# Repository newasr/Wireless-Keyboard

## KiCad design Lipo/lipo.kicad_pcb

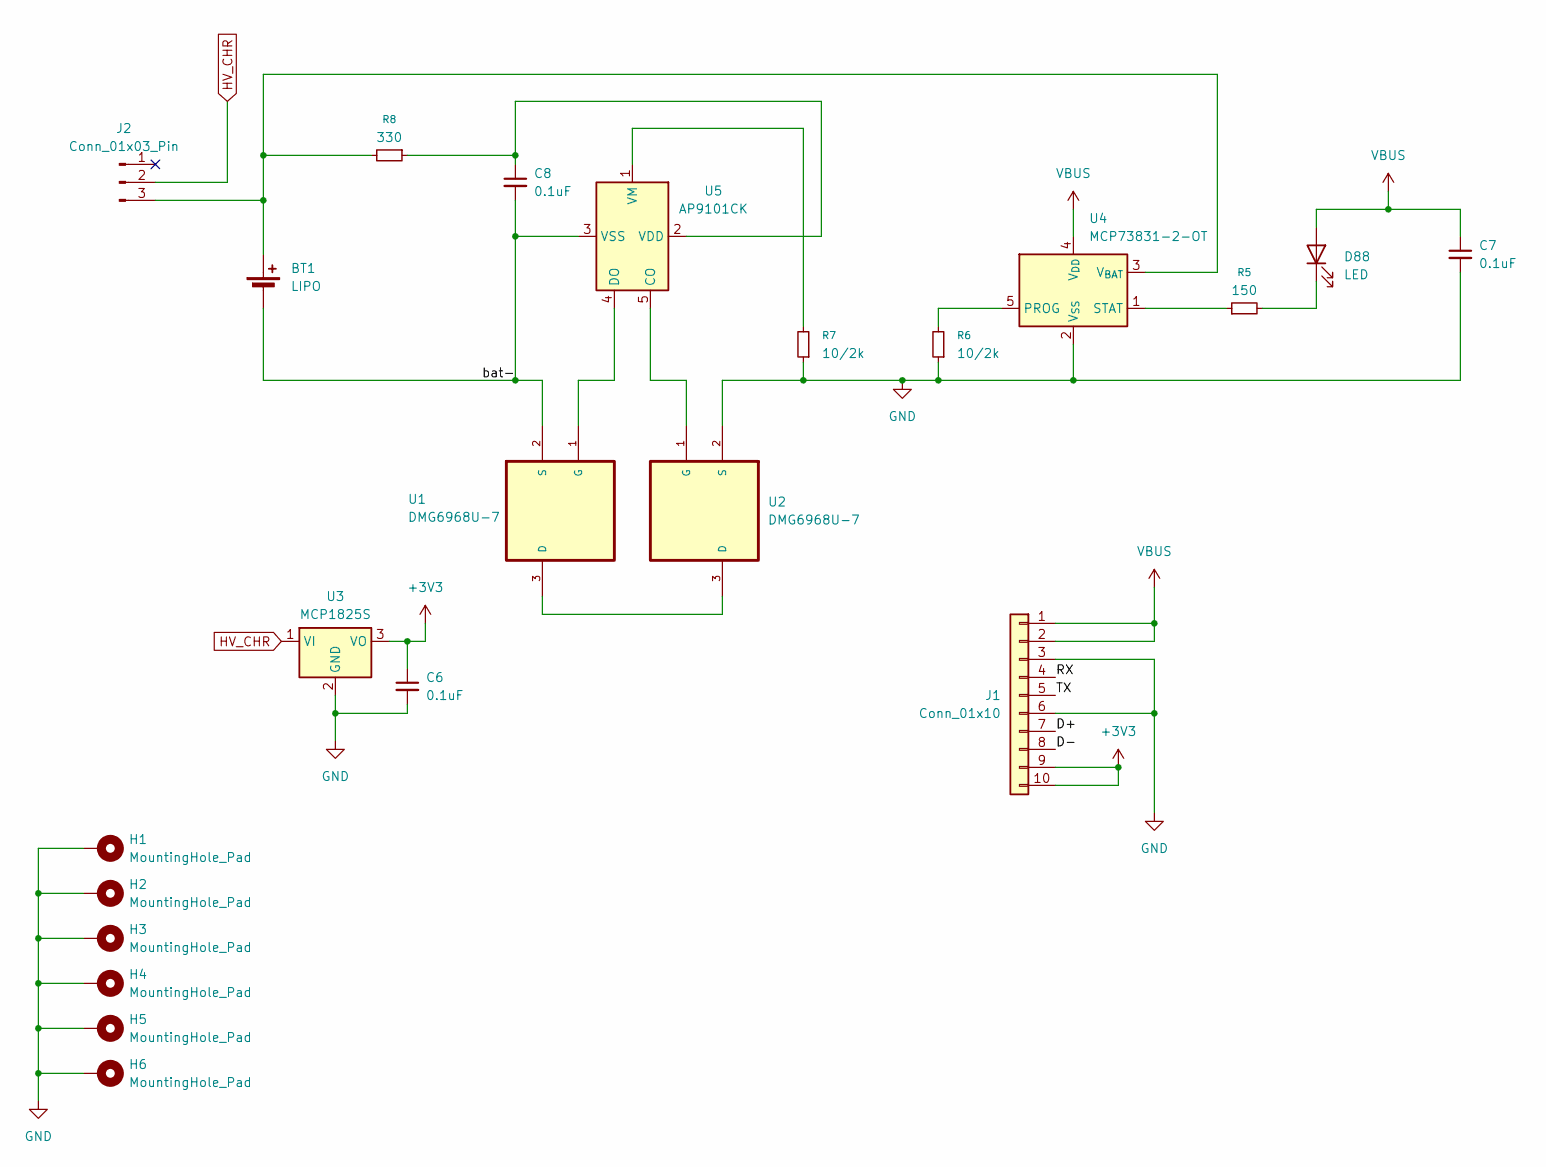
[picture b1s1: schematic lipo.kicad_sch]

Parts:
BT1: LIPO; PinHeader_1x02_P2.54mm_Vertical_SMD_Pin1Left
C6, C7, C8: 0.1uF; C_0201_0603Metric
D88: LED; LED_0603_1608Metric
H1, H2, H3, H4, H5, H6: MountingHole_Pad; MountingHole_3.2mm_M3_DIN965_Pad
J1: Conn_01x10; Molex_200528-0100_1x10-1MP_P1.00mm_Horizontal
J2: Conn_01x03_Pin; PinHeader_1x03_P2.54mm_Vertical_SMD_Pin1Left
R5: 150; R_0201_0603Metric
R6, R7: 10/2k; R_0201_0603Metric
R8: 330; R_0201_0603Metric
U1, U2: DMG6968U-7; dmg6968U7; MPN DMG6968U-7
U3: MCP1825S; SOT-223-3_TabPin2
U4: MCP73831-2-OT; SOT-23-5
U5: AP9101CK; SOT-23-5

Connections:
+3V3: C6.1, J1.9, J1.10, U3.3 (VO)
/D+: J1.7
/D-: J1.8
/RX: J1.4
/TX: J1.5
/bat-: BT1.2 (-), C8.2, U1.2 (S), U5.3 (VSS)
GND: C6.2, C7.2, H1.1, H2.1, H3.1, H4.1, H5.1, H6.1, J1.3, J1.6, R6.1, R7.1, U2.2 (S), U3.2 (GND), U4.2 (V_{SS})
HV_CHR: J2.2, U3.1 (VI)
unnamed: BT1.1 (+), J2.3, R8.2, U4.3 (V_{BAT})
unnamed: D88.1 (K), R5.2
unnamed: U1.3 (D), U2.3 (D)
unnamed: U1.1 (G), U5.4 (DO)
unnamed: U2.1 (G), U5.5 (CO)
unnamed: R6.2, U4.5 (PROG)
unnamed: R5.1, U4.1 (STAT)
unnamed: C8.1, R8.1, U5.2 (VDD)
unnamed: R7.2, U5.1 (VM)
VBUS: C7.1, D88.2 (A), J1.1, J1.2, U4.4 (V_{DD})

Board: 2 copper layers, 22 parts (0 on the bottom side), 14 nets, no tracks yet.

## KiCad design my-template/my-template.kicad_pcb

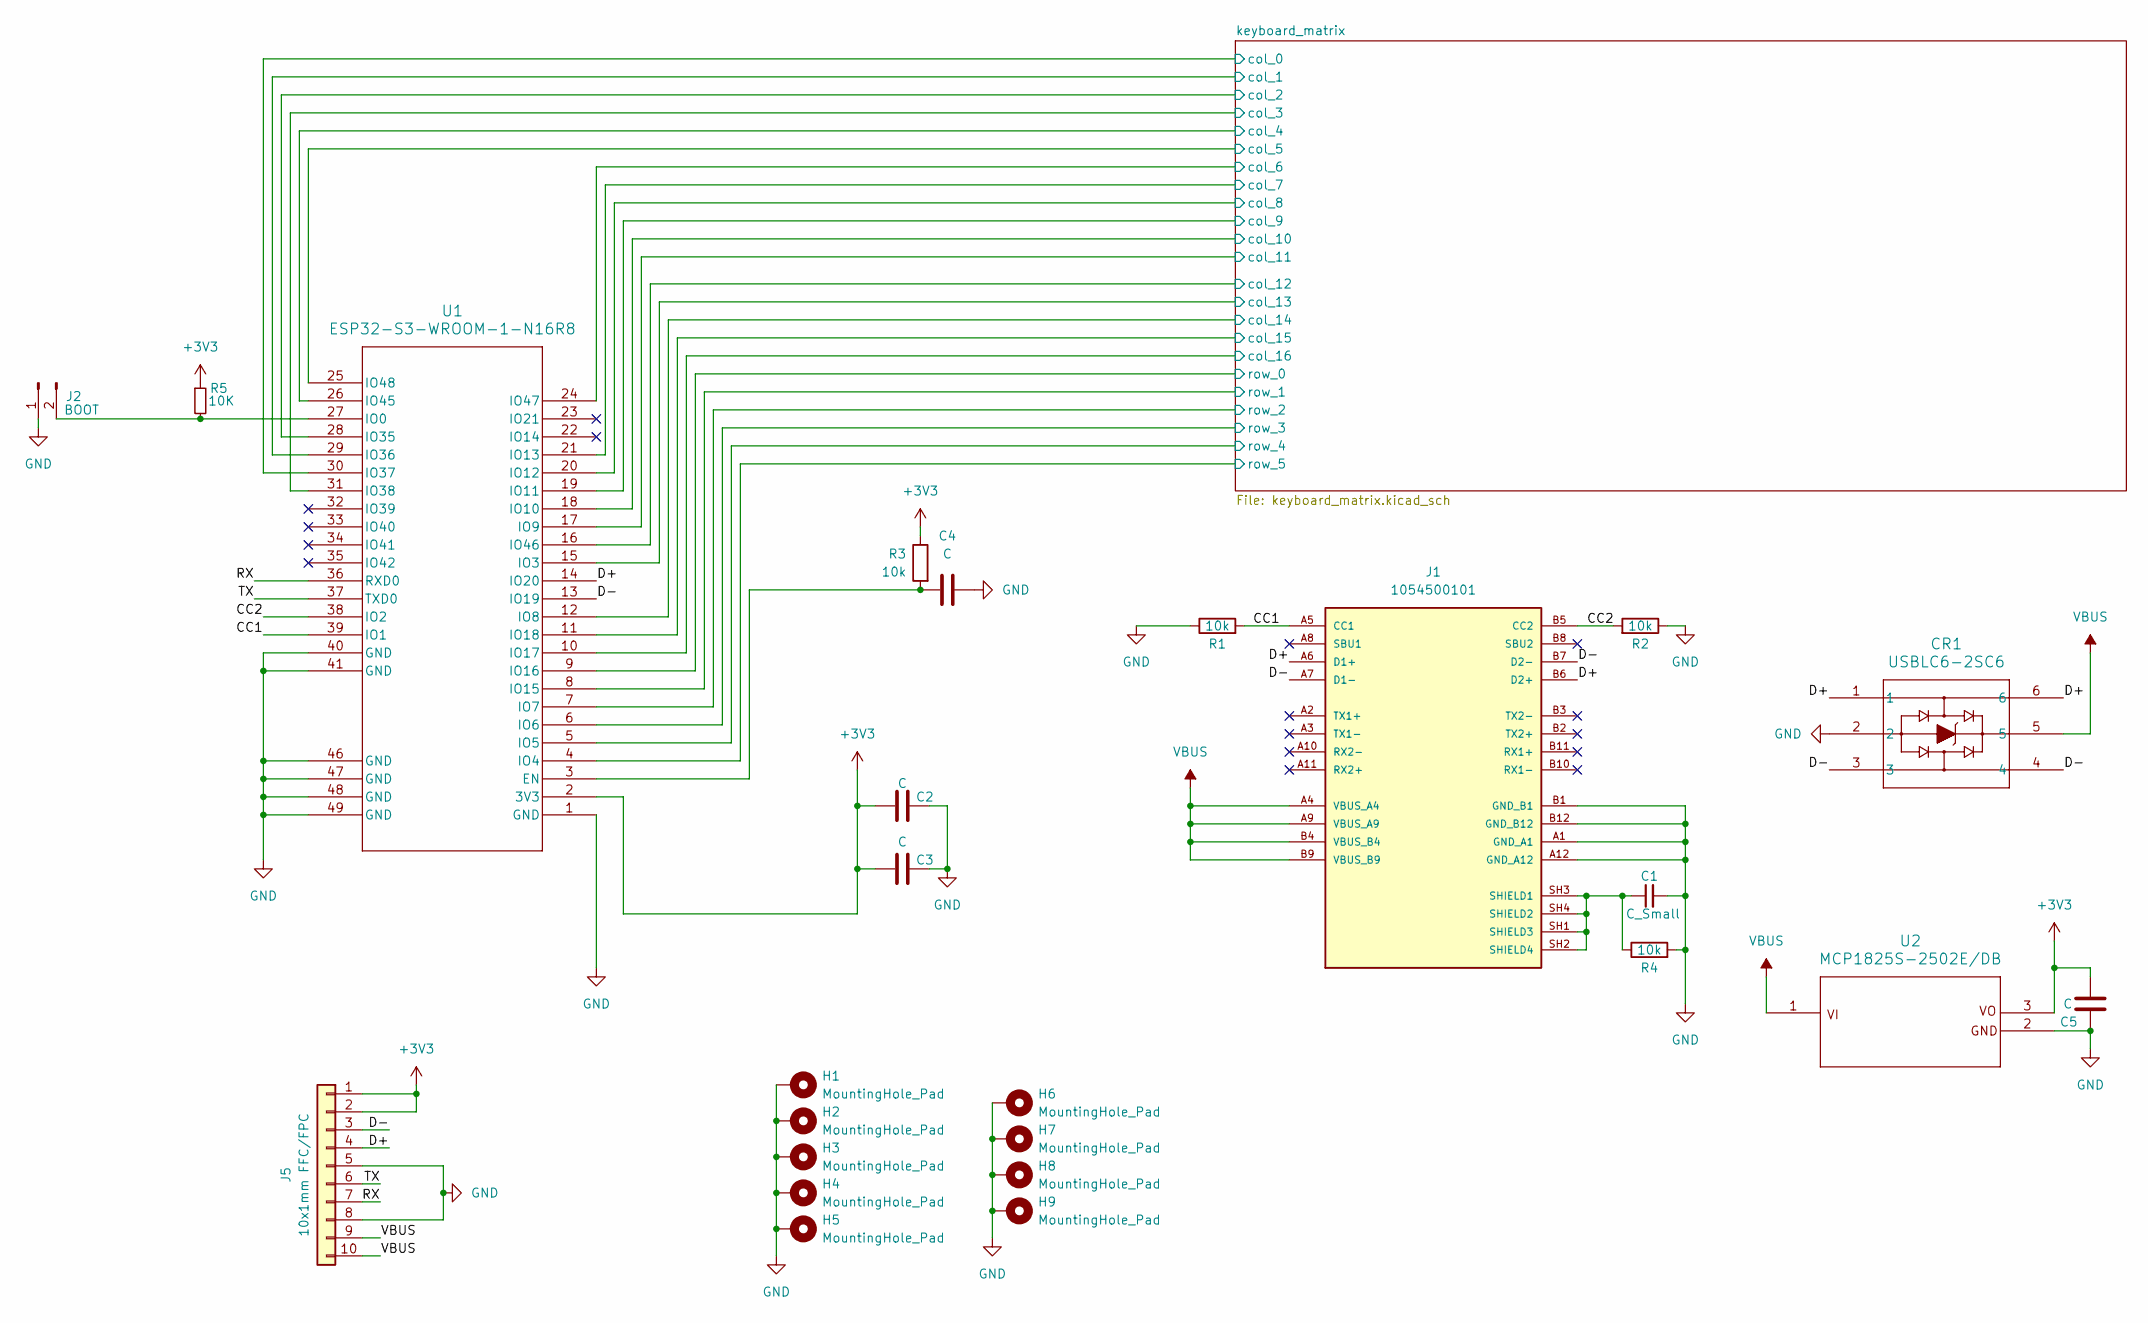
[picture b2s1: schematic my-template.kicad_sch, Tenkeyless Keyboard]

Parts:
C1: C_Small; C_0603_1608Metric
C2, C3, C4, C5: C; C_0603_1608Metric
CR1: USBLC6-2SC6
H1, H2, H3, H4, H5, H6, H7, H8, H9: MountingHole_Pad; MountingHole_3.2mm_M3_DIN965_Pad
J1: 1054500101; MOLEX_1054500101; PARTREV A7
J2: BOOT; PinHeader_1x02_P2.54mm_Horizontal
J5: 10x1mm FFC/FPC; Molex_200528-0100_1x10-1MP_P1.00mm_Horizontal
R1, R2, R3, R4: 10k; R_0603_1608Metric
R5: 10K; R_0603_1608Metric
U1: ESP32-S3-WROOM-1-N16R8; ESP32-S3-WROOM-1_EXP
U2: MCP1825S-2502E/DB; SOT-223_3MC_MCH

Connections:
+3V3: C2.1, C3.1, C5.1, J5.1, J5.2, R3.1, R5.1, U1.2 (3V3), U2.3
/CC1: J1.A5 (CC1), R1.2, U1.39 (IO1)
/CC2: J1.B5 (CC2), R2.2, U1.38 (IO2)
/D+: CR1.1, CR1.6, J1.A6 (D1+), J1.B6 (D2+), J5.4, U1.14 (IO20)
/D-: CR1.3, CR1.4, J1.A7 (D1-), J1.B7 (D2-), J5.3, U1.13 (IO19)
/RX: J5.7, U1.36 (RXD0)
/TX: J5.6, U1.37 (TXD0)
/keyboard_matrix/col_0: U1.30 (IO37); also elsewhere on the board
/keyboard_matrix/col_1: U1.29 (IO36); also elsewhere on the board
/keyboard_matrix/col_2: U1.28 (IO35); also elsewhere on the board
/keyboard_matrix/col_3: U1.31 (IO38); also elsewhere on the board
/keyboard_matrix/col_4: U1.26 (IO45); also elsewhere on the board
/keyboard_matrix/col_5: U1.25 (IO48); also elsewhere on the board
/keyboard_matrix/col_6: U1.24 (IO47); also elsewhere on the board
/keyboard_matrix/col_7: U1.21 (IO13); also elsewhere on the board
/keyboard_matrix/col_8: U1.20 (IO12); also elsewhere on the board
/keyboard_matrix/col_9: U1.19 (IO11); also elsewhere on the board
/keyboard_matrix/col_10: U1.18 (IO10); also elsewhere on the board
/keyboard_matrix/col_11: U1.17 (IO9); also elsewhere on the board
/keyboard_matrix/col_12: U1.16 (IO46); also elsewhere on the board
/keyboard_matrix/col_13: U1.15 (IO3); also elsewhere on the board
/keyboard_matrix/col_14: U1.12 (IO8); also elsewhere on the board
/keyboard_matrix/col_15: U1.11 (IO18); also elsewhere on the board
/keyboard_matrix/col_16: U1.10 (IO17); also elsewhere on the board
/keyboard_matrix/row_0: U1.9 (IO16); also elsewhere on the board
/keyboard_matrix/row_1: U1.8 (IO15); also elsewhere on the board
/keyboard_matrix/row_2: U1.7 (IO7); also elsewhere on the board
/keyboard_matrix/row_3: U1.6 (IO6); also elsewhere on the board
/keyboard_matrix/row_4: U1.5 (IO5); also elsewhere on the board
/keyboard_matrix/row_5: U1.4 (IO4); also elsewhere on the board
GND: C1.2, C2.2, C3.2, C4.2, C5.2, CR1.2, H1.1, H2.1, H3.1, H4.1, H5.1, H6.1, H7.1, H8.1, H9.1, J1.A1 (GND_A1), J1.A12 (GND_A12), J1.B1 (GND_B1), J1.B12 (GND_B12), J2.1, J5.5, J5.8, R1.1, R2.1, R4.2, U1.1 (GND), U1.40 (GND), U1.41 (GND), U1.46 (GND), U1.47 (GND), U1.48 (GND), U1.49 (GND), U2.2
unnamed: C1.1, J1.SH1 (SHIELD3), J1.SH2 (SHIELD4), J1.SH3 (SHIELD1), J1.SH4 (SHIELD2), R4.1
unnamed: J2.2, R5.2, U1.27 (IO0)
unnamed: C4.1, R3.2, U1.3 (EN)
VBUS: CR1.5, J1.A4 (VBUS_A4), J1.A9 (VBUS_A9), J1.B4 (VBUS_B4), J1.B9 (VBUS_B9), J5.9, J5.10, U2.1

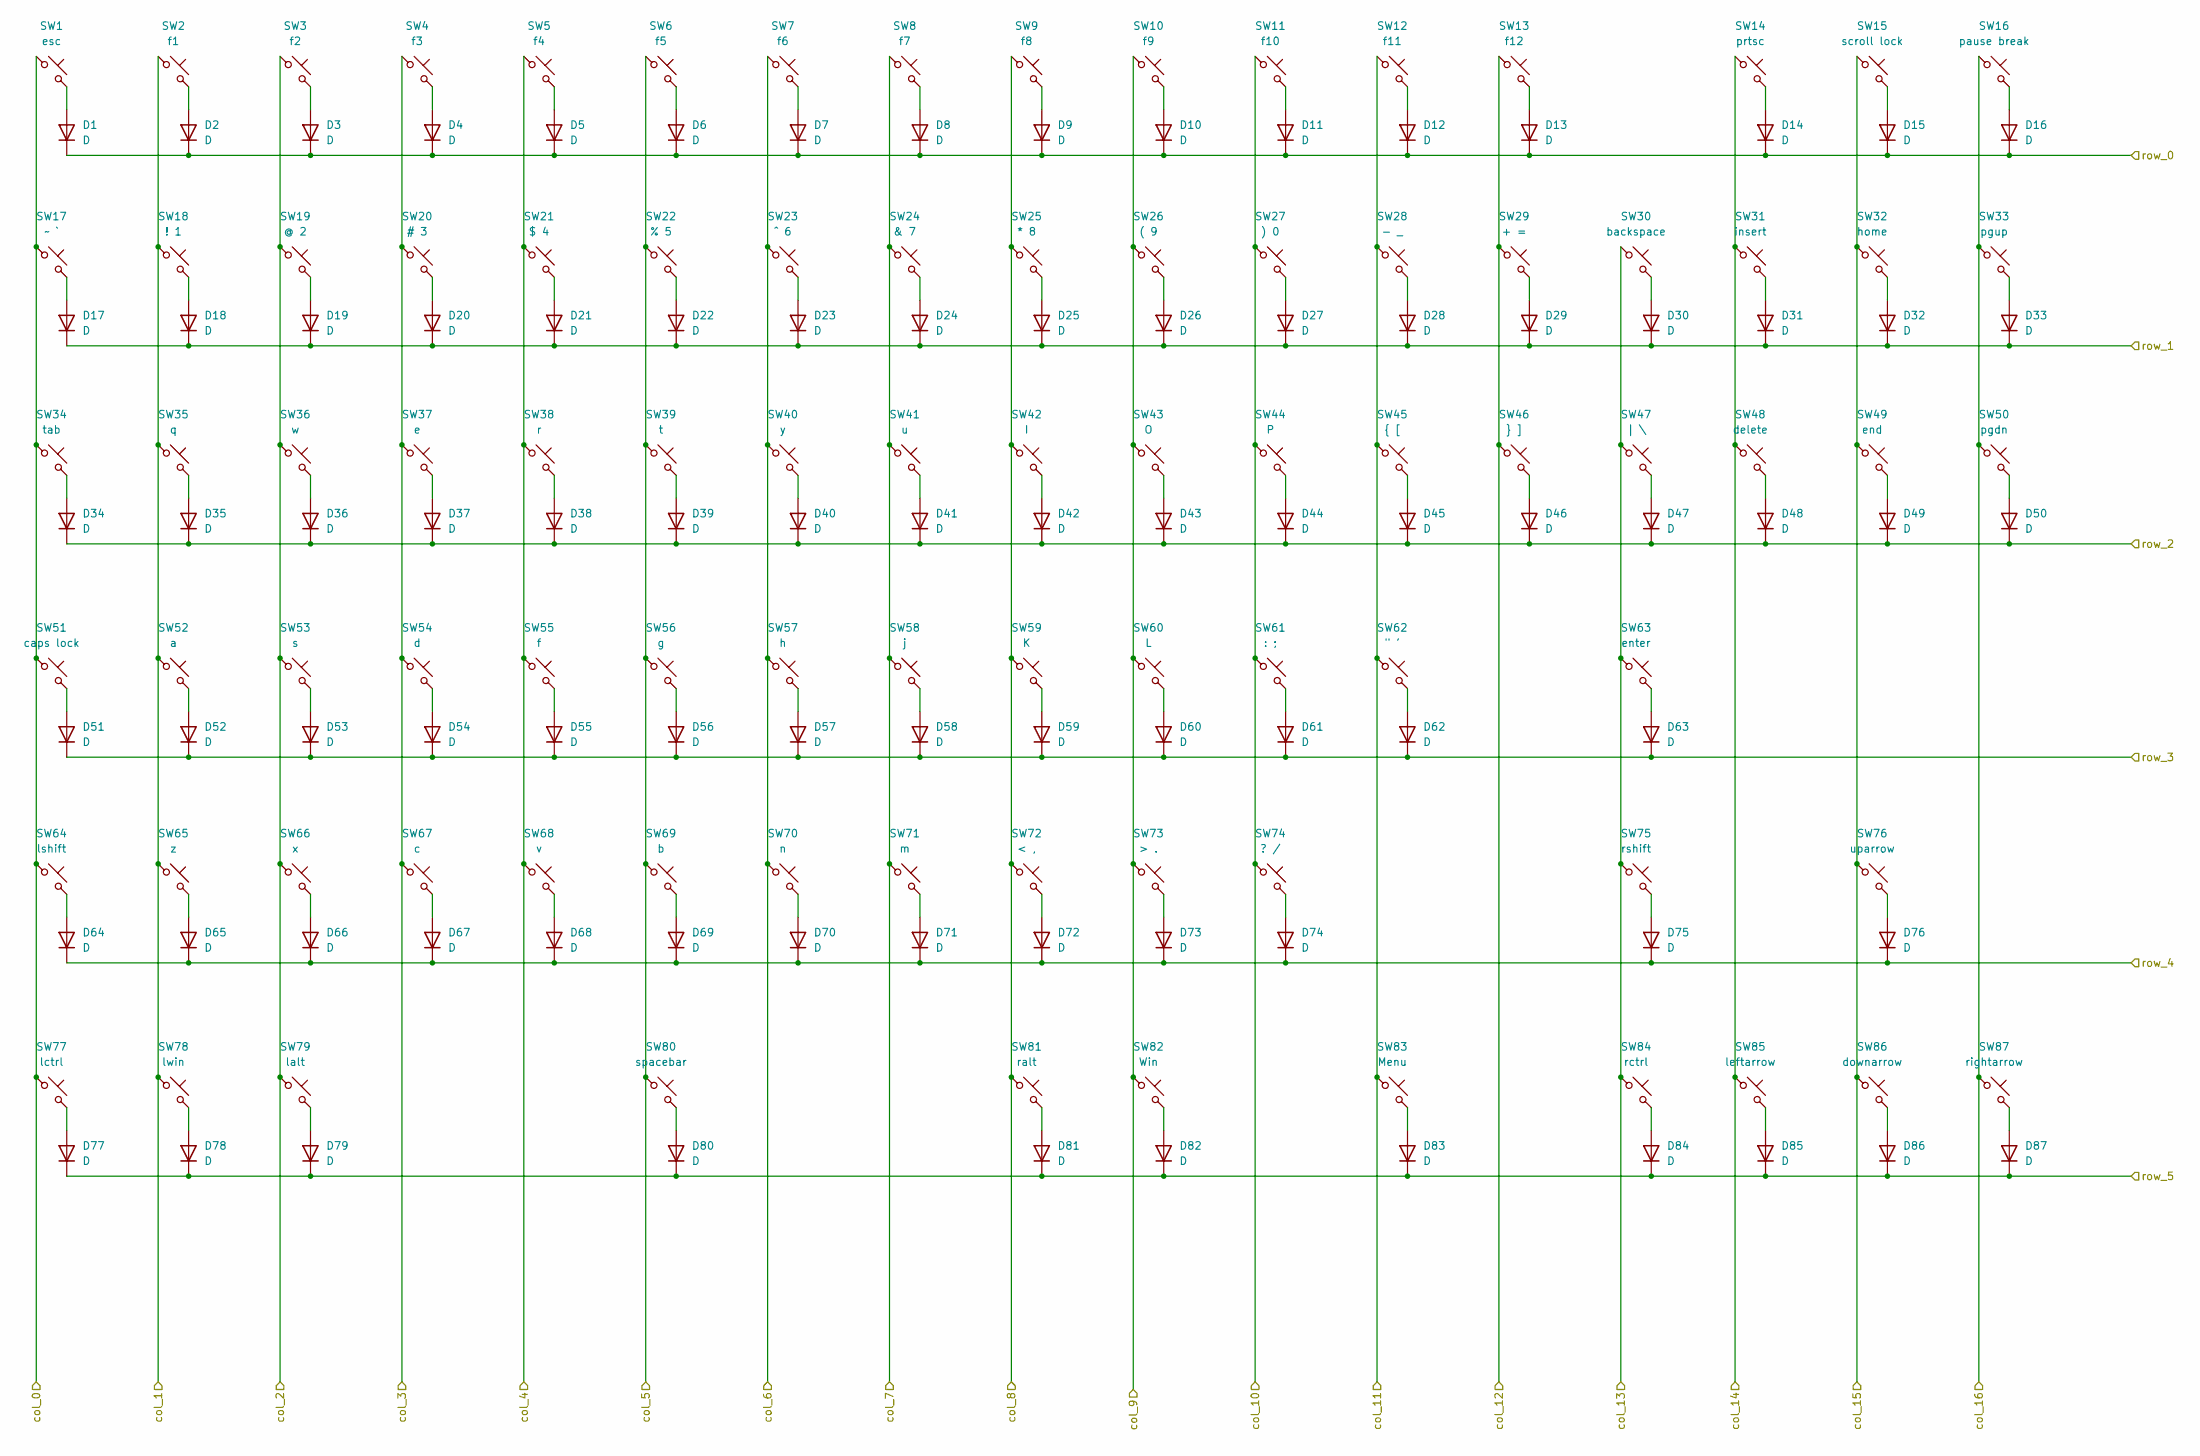
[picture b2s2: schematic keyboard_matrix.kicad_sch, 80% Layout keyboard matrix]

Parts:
D1, D2, D3, D4, D5, D6, D7, D8, D9, D10, D11, D12, D13, D14, D15, D16, D17, D18, D19, D20, D21, D22, D23, D24, D25, D26, D27, D28, D29, D30, D31, D32, D33, D34, D35, D36, D37, D38, D39, D40, D41, D42, D43, D44, D45, D46, D47, D48, D49, D50, D51, D52, D53, D54, D55, D56, D57, D58, D59, D60, D61, D62, D63, D64, D65, D66, D67, D68, D69, D70, D71, D72, D73, D74, D75, D76, D77, D78, D79, D80, D81, D82, D83, D84, D85, D86, D87: D; D_SOD-123
SW1: esc; MX_PCB_1.00u
SW2: f1; MX_PCB_1.00u
SW3: f2; MX_PCB_1.00u
SW4: f3; MX_PCB_1.00u
SW5: f4; MX_PCB_1.00u
SW6: f5; MX_PCB_1.00u
SW7: f6; MX_PCB_1.00u
SW8: f7; MX_PCB_1.00u
SW9: f8; MX_PCB_1.00u
SW10: f9; MX_PCB_1.00u
SW11: f10; MX_PCB_1.00u
SW12: f11; MX_PCB_1.00u
SW13: f12; MX_PCB_1.00u
SW14: prtsc; MX_PCB_1.00u
SW15: scroll lock; MX_PCB_1.00u
SW16: pause break; MX_PCB_1.00u
SW17: ~ `; MX_PCB_1.00u
SW18: ! 1; MX_PCB_1.00u
SW19: @ 2; MX_PCB_1.00u
SW20: # 3; MX_PCB_1.00u
SW21: $ 4; MX_PCB_1.00u
SW22: % 5; MX_PCB_1.00u
SW23: ^ 6; MX_PCB_1.00u
SW24: & 7; MX_PCB_1.00u
SW25: * 8; MX_PCB_1.00u
SW26: ( 9; MX_PCB_1.00u
SW27: ) 0; MX_PCB_1.00u
SW28: - _; MX_PCB_1.00u
SW29: + =; MX_PCB_1.00u
SW30: backspace; MX_PCB_2.00u
SW31: insert; MX_PCB_1.00u
SW32: home; MX_PCB_1.00u
SW33: pgup; MX_PCB_1.00u
SW34: tab; MX_PCB_1.50u
SW35: q; MX_PCB_1.00u
SW36: w; MX_PCB_1.00u
SW37: e; MX_PCB_1.00u
SW38: r; MX_PCB_1.00u
SW39: t; MX_PCB_1.00u
SW40: y; MX_PCB_1.00u
SW41: u; MX_PCB_1.00u
SW42: I; MX_PCB_1.00u
SW43: O; MX_PCB_1.00u
SW44: P; MX_PCB_1.00u
SW45: { [; MX_PCB_1.00u
SW46: } ]; MX_PCB_1.00u
SW47: | \; MX_PCB_1.50u
SW48: delete; MX_PCB_1.00u
SW49: end; MX_PCB_1.00u
SW50: pgdn; MX_PCB_1.00u
SW51: caps lock; MX_PCB_1.00u
SW52: a; MX_PCB_1.00u
SW53: s; MX_PCB_1.00u
SW54: d; MX_PCB_1.00u
SW55: f; MX_PCB_1.00u
SW56: g; MX_PCB_1.00u
SW57: h; MX_PCB_1.00u
SW58: j; MX_PCB_1.00u
SW59: K; MX_PCB_1.00u
SW60: L; MX_PCB_1.00u
SW61: : ;; MX_PCB_1.00u
SW62: " '; MX_PCB_1.00u
SW63: enter; MX_PCB_2.25u
SW64: lshift; MX_PCB_2.25u
SW65: z; MX_PCB_1.00u
SW66: x; MX_PCB_1.00u
SW67: c; MX_PCB_1.00u
SW68: v; MX_PCB_1.00u
SW69: b; MX_PCB_1.00u
SW70: n; MX_PCB_1.00u
SW71: m; MX_PCB_1.00u
SW72: < ,; MX_PCB_1.00u
SW73: > .; MX_PCB_1.00u
SW74: ? /; MX_PCB_1.00u
SW75: rshift; MX_PCB_2.75u
SW76: uparrow; MX_PCB_1.00u
SW77: lctrl; MX_PCB_1.25u
SW78: lwin; MX_PCB_1.25u
SW79: lalt; MX_PCB_1.25u
SW80: spacebar; MX_PCB_6.25u
SW81: ralt; MX_PCB_1.25u
SW82: Win; MX_PCB_1.25u
SW83: Menu; MX_PCB_1.25u
SW84: rctrl; MX_PCB_1.25u
SW85: leftarrow; MX_PCB_1.00u
SW86: downarrow; MX_PCB_1.00u
SW87: rightarrow; MX_PCB_1.00u

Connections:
/keyboard_matrix/col_0: SW1.1, SW17.1, SW34.1, SW51.1, SW64.1, SW77.1; also elsewhere on the board
/keyboard_matrix/col_1: SW2.1, SW18.1, SW35.1, SW52.1, SW65.1, SW78.1; also elsewhere on the board
/keyboard_matrix/col_2: SW3.1, SW19.1, SW36.1, SW53.1, SW66.1, SW79.1; also elsewhere on the board
/keyboard_matrix/col_3: SW4.1, SW20.1, SW37.1, SW54.1, SW67.1; also elsewhere on the board
/keyboard_matrix/col_4: SW5.1, SW21.1, SW38.1, SW55.1, SW68.1; also elsewhere on the board
/keyboard_matrix/col_5: SW6.1, SW22.1, SW39.1, SW56.1, SW69.1, SW80.1; also elsewhere on the board
/keyboard_matrix/col_6: SW7.1, SW23.1, SW40.1, SW57.1, SW70.1; also elsewhere on the board
/keyboard_matrix/col_7: SW8.1, SW24.1, SW41.1, SW58.1, SW71.1; also elsewhere on the board
/keyboard_matrix/col_8: SW9.1, SW25.1, SW42.1, SW59.1, SW72.1, SW81.1; also elsewhere on the board
/keyboard_matrix/col_9: SW10.1, SW26.1, SW43.1, SW60.1, SW73.1, SW82.1; also elsewhere on the board
/keyboard_matrix/col_10: SW11.1, SW27.1, SW44.1, SW61.1, SW74.1; also elsewhere on the board
/keyboard_matrix/col_11: SW12.1, SW28.1, SW45.1, SW62.1, SW83.1; also elsewhere on the board
/keyboard_matrix/col_12: SW13.1, SW29.1, SW46.1; also elsewhere on the board
/keyboard_matrix/col_13: SW30.1, SW47.1, SW63.1, SW75.1, SW84.1; also elsewhere on the board
/keyboard_matrix/col_14: SW14.1, SW31.1, SW48.1, SW85.1; also elsewhere on the board
/keyboard_matrix/col_15: SW15.1, SW32.1, SW49.1, SW76.1, SW86.1; also elsewhere on the board
/keyboard_matrix/col_16: SW16.1, SW33.1, SW50.1, SW87.1; also elsewhere on the board
/keyboard_matrix/row_0: D1.1 (K), D2.1 (K), D3.1 (K), D4.1 (K), D5.1 (K), D6.1 (K), D7.1 (K), D8.1 (K), D9.1 (K), D10.1 (K), D11.1 (K), D12.1 (K), D13.1 (K), D14.1 (K), D15.1 (K), D16.1 (K); also elsewhere on the board
/keyboard_matrix/row_1: D17.1 (K), D18.1 (K), D19.1 (K), D20.1 (K), D21.1 (K), D22.1 (K), D23.1 (K), D24.1 (K), D25.1 (K), D26.1 (K), D27.1 (K), D28.1 (K), D29.1 (K), D30.1 (K), D31.1 (K), D32.1 (K), D33.1 (K); also elsewhere on the board
/keyboard_matrix/row_2: D34.1 (K), D35.1 (K), D36.1 (K), D37.1 (K), D38.1 (K), D39.1 (K), D40.1 (K), D41.1 (K), D42.1 (K), D43.1 (K), D44.1 (K), D45.1 (K), D46.1 (K), D47.1 (K), D48.1 (K), D49.1 (K), D50.1 (K); also elsewhere on the board
/keyboard_matrix/row_3: D51.1 (K), D52.1 (K), D53.1 (K), D54.1 (K), D55.1 (K), D56.1 (K), D57.1 (K), D58.1 (K), D59.1 (K), D60.1 (K), D61.1 (K), D62.1 (K), D63.1 (K); also elsewhere on the board
/keyboard_matrix/row_4: D64.1 (K), D65.1 (K), D66.1 (K), D67.1 (K), D68.1 (K), D69.1 (K), D70.1 (K), D71.1 (K), D72.1 (K), D73.1 (K), D74.1 (K), D75.1 (K), D76.1 (K); also elsewhere on the board
/keyboard_matrix/row_5: D77.1 (K), D78.1 (K), D79.1 (K), D80.1 (K), D81.1 (K), D82.1 (K), D83.1 (K), D84.1 (K), D85.1 (K), D86.1 (K), D87.1 (K); also elsewhere on the board
unnamed: D1.2 (A), SW1.2
unnamed: D2.2 (A), SW2.2
unnamed: D3.2 (A), SW3.2
unnamed: D4.2 (A), SW4.2
unnamed: D5.2 (A), SW5.2
unnamed: D6.2 (A), SW6.2
unnamed: D7.2 (A), SW7.2
unnamed: D8.2 (A), SW8.2
unnamed: D9.2 (A), SW9.2
unnamed: D10.2 (A), SW10.2
unnamed: D11.2 (A), SW11.2
unnamed: D12.2 (A), SW12.2
unnamed: D13.2 (A), SW13.2
unnamed: D14.2 (A), SW14.2
unnamed: D15.2 (A), SW15.2
unnamed: D16.2 (A), SW16.2
unnamed: D17.2 (A), SW17.2
unnamed: D18.2 (A), SW18.2
unnamed: D19.2 (A), SW19.2
unnamed: D20.2 (A), SW20.2
unnamed: D21.2 (A), SW21.2
unnamed: D22.2 (A), SW22.2
unnamed: D23.2 (A), SW23.2
unnamed: D24.2 (A), SW24.2
unnamed: D25.2 (A), SW25.2
unnamed: D26.2 (A), SW26.2
unnamed: D27.2 (A), SW27.2
unnamed: D28.2 (A), SW28.2
unnamed: D29.2 (A), SW29.2
unnamed: D30.2 (A), SW30.2
unnamed: D31.2 (A), SW31.2
unnamed: D32.2 (A), SW32.2
unnamed: D33.2 (A), SW33.2
unnamed: D34.2 (A), SW34.2
unnamed: D35.2 (A), SW35.2
unnamed: D36.2 (A), SW36.2
unnamed: D37.2 (A), SW37.2
unnamed: D38.2 (A), SW38.2
unnamed: D39.2 (A), SW39.2
unnamed: D40.2 (A), SW40.2
unnamed: D41.2 (A), SW41.2
unnamed: D42.2 (A), SW42.2
unnamed: D43.2 (A), SW43.2
unnamed: D44.2 (A), SW44.2
unnamed: D45.2 (A), SW45.2
unnamed: D46.2 (A), SW46.2
unnamed: D47.2 (A), SW47.2
unnamed: D48.2 (A), SW48.2
unnamed: D49.2 (A), SW49.2
unnamed: D50.2 (A), SW50.2
unnamed: D51.2 (A), SW51.2
unnamed: D52.2 (A), SW52.2
unnamed: D53.2 (A), SW53.2
unnamed: D54.2 (A), SW54.2
unnamed: D55.2 (A), SW55.2
unnamed: D56.2 (A), SW56.2
unnamed: D57.2 (A), SW57.2
unnamed: D58.2 (A), SW58.2
unnamed: D59.2 (A), SW59.2
unnamed: D60.2 (A), SW60.2
unnamed: D61.2 (A), SW61.2
unnamed: D62.2 (A), SW62.2
unnamed: D63.2 (A), SW63.2
unnamed: D64.2 (A), SW64.2
unnamed: D65.2 (A), SW65.2
unnamed: D66.2 (A), SW66.2
unnamed: D67.2 (A), SW67.2
unnamed: D68.2 (A), SW68.2
unnamed: D69.2 (A), SW69.2
unnamed: D70.2 (A), SW70.2
unnamed: D71.2 (A), SW71.2
unnamed: D72.2 (A), SW72.2
unnamed: D73.2 (A), SW73.2
unnamed: D74.2 (A), SW74.2
unnamed: D75.2 (A), SW75.2
unnamed: D76.2 (A), SW76.2
unnamed: D77.2 (A), SW77.2
unnamed: D78.2 (A), SW78.2
unnamed: D79.2 (A), SW79.2
unnamed: D80.2 (A), SW80.2
unnamed: D81.2 (A), SW81.2
unnamed: D82.2 (A), SW82.2
unnamed: D83.2 (A), SW83.2
unnamed: D84.2 (A), SW84.2
unnamed: D85.2 (A), SW85.2
unnamed: D86.2 (A), SW86.2
unnamed: D87.2 (A), SW87.2

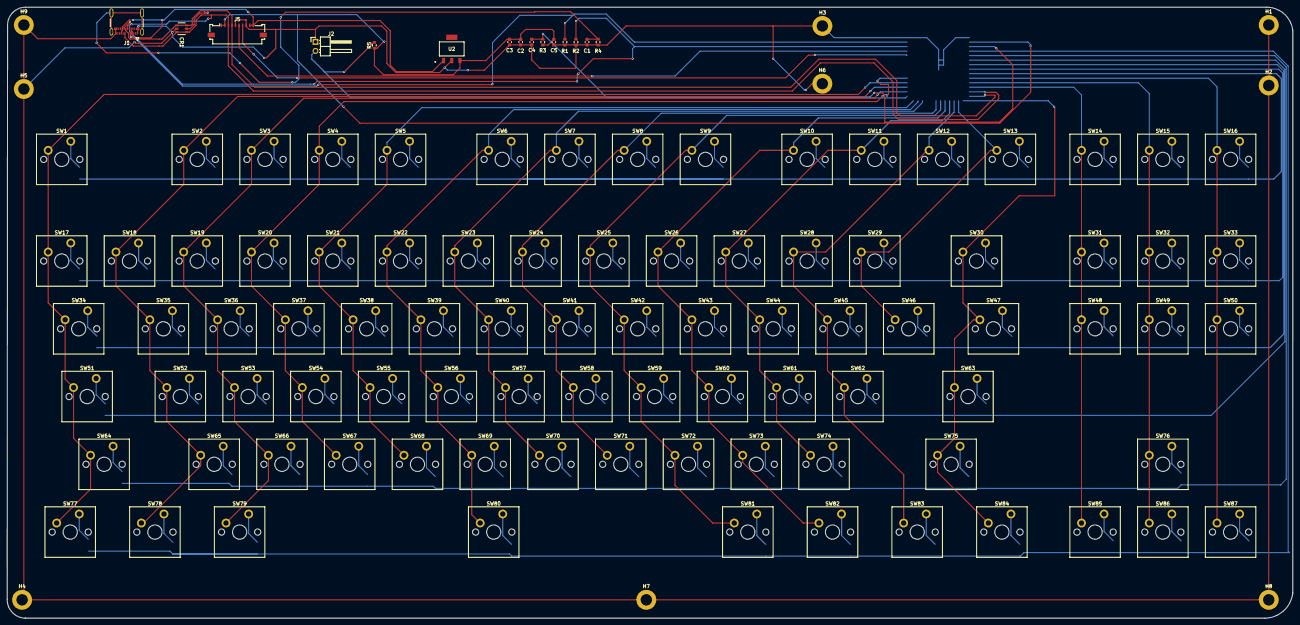
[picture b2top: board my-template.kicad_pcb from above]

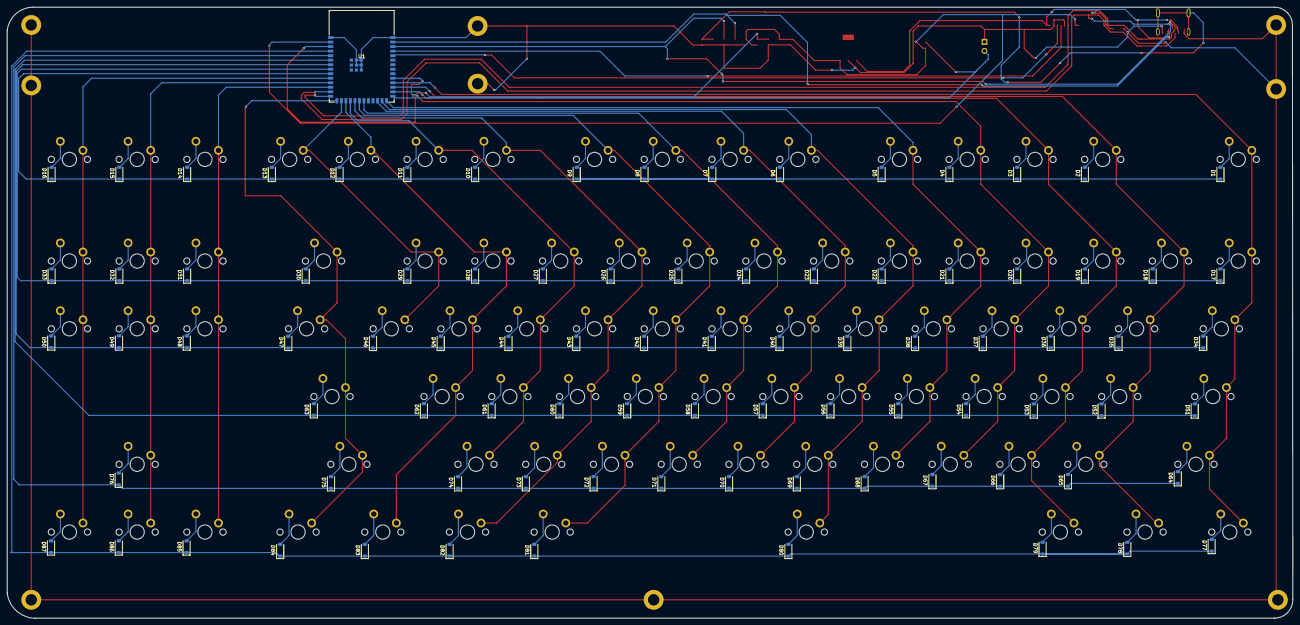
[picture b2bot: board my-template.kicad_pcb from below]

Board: 2 copper layers, 361.4 x 171.8 mm, 199 parts (88 on the bottom side), 122 nets.

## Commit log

2025-04-04 keyboard matrix and esp circuit done
2025-04-05 lipo schematic done
2025-04-05 resolved warnings in esp circuit
2025-04-05 component placement done
2025-04-05 started pcb routing, 63 connections left
2025-04-06 keyboard routing done, lipo remaining
2025-04-06 resolved erc errors in lip and added footprint
